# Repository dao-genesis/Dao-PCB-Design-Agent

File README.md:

# Dao-PCB-Design-Agent

> 让 Agent 像 Cursor 写代码一样进入 EDA 底层,代替人类全流程、全模块推进 PCB 设计。
> 道法自然 · 无为而无不为。

一个仓库,**两条并行且互不耦合的演化路线**(鸡犬相闻,老死不相往来):各自独立入口、
各自依赖、互不破坏,可单独演进,也可在数据层串联。

```
                         Dao-PCB-Design-Agent
                                  │
          ┌───────────────────────┴───────────────────────┐
          ▼                                                 ▼
  路线 A · 嘉立创EDA 直连                          路线 B · KiCad / 代码化
  (在线 Web 编辑器, CDP 直驱)                      (本地引擎, 代码生成 PCB)
          │                                                 │
   lceda_bridge/                                  pcb_brain/   (21 DNA 模板 → .kicad_pcb/Gerber/BOM)
     └ cdp_studio/  ← 冷启动底座                  schematic_dao/ (原理图道 → 四件套资料包)
       (CDP 直驱 _EXTAPI_ROOT_ + 登录态固化)       kicad_origin/  (KiCad 本源直连)
```

---

## 路线 A · 嘉立创EDA 直连(在线 Web · CDP)

经 Chrome 远程调试(CDP)在 `pro.lceda.cn/editor` 主页面上下文直接调用官方扩展 API
(挂在 `window._EXTAPI_ROOT_`,91 个命名空间),无需安装扩展/沙箱,执行→反馈→呈现三面归一。

- **冷启动底座**:[`lceda_bridge/cdp_studio/`](./lceda_bridge/cdp_studio/README.md) ——
  全新 VM 一条命令落到"已登录、可直驱"状态:
  ```bash
  python lceda_bridge/cdp_studio/cold_start.py
  ```
  登录态/凭据走加密 secret(`JLC_PHONE` / `JLC_PASSWORD` / `JLC_SESSION_B64`)注入,
  仓库内不存任何明文。后续会话只需手机号+密码即可承接。
- **桥接全景**:[`lceda_bridge/README.md`](./lceda_bridge/README.md)(五层穿透)。

## 路线 B · KiCad / 代码化(本地引擎)

代码即电路:从 DNA 模板/原理图工程一键生成可打样的 PCB 与全套制造资料。

- **PCBBrain**:[`pcb_brain/`](./pcb_brain/) —— 21 个 DNA 模板 → `.kicad_pcb`/Gerber/BOM/iBoM。
  ```python
  from pcb_core import PCB        # 统一门面
  ```
- **原理图道**:[`schematic_dao/`](./schematic_dao/) —— `SchematicProject` → 论文级四件套。
  ```bash
  python -m schematic_dao build <project>
  ```
- **KiCad 本源**:[`kicad_origin/`](./kicad_origin/)。

> 两线可在数据层串联:SchematicProject(论文级)→ DNA(布局级)→ PCB 打样下单。

---

## 仓库导航

| 目录 | 路线 | 说明 |
|---|---|---|
| `lceda_bridge/` | A | 嘉立创EDA 直连 + 冷启动底座(`cdp_studio/`) |
| `pcb_brain/` | B | DNA 模板 + 全闭环流水线(PCB) |
| `schematic_dao/` | B | 原理图道(四件套资料包) |
| `kicad_origin/` | B | KiCad 本源直连 |
| `_JLC_READY/` | 共用 | 23 个成品板模板(嘉立创打样就绪) |
| `实战/` | 共用 | 实战项目(1500W PFC、物流车控制系统等) |
| `docs/` | — | 总体方案与调研(全链路实现方案、线上资源参考) |
| `_local_launchers/` | — | 用户本机桌面启动器(指向本地 `D:\`/`Z:\` 路径,仅本机可用) |

- 架构与资源总览:[`_INDEX.md`](./_INDEX.md)
- Agent 操作手册:[`_AGENT_GUIDE.md`](./_AGENT_GUIDE.md)
- 交接说明:[`HANDOFF.md`](./HANDOFF.md)

## 仓库内入口脚本

- `lceda.cmd` / `lceda.ps1` —— LCEDA Bridge CLI(`lceda <subcmd>`,任意目录可用)。

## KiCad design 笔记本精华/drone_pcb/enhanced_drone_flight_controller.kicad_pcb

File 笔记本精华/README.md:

# 📁 项目模板说明

这个目录包含了各种SKiDL项目模板，帮助您快速开始新的PCB设计项目。

## 🎯 可用模板

### 1. **新项目模板.py** ⭐
- **用途**: 通用项目起始模板
- **包含**: 基础电路结构、LED控制、电源管理
- **特点**: 完整的注释、错误处理、自动化输出

### 2. **即将添加的模板**:
- `微控制器项目模板.py` - MCU核心电路
- `电源管理模板.py` - 电源转换电路  
- `传感器接口模板.py` - 传感器连接电路
- `通信接口模板.py` - UART/SPI/I2C接口

## 🚀 使用方法

### 快速开始
```bash
# 1. 复制模板到项目目录
cp templates/新项目模板.py projects/我的新项目.py

# 2. 编辑项目信息
# 修改文件中的PROJECT_NAME、AUTHOR等变量

# 3. 运行项目
cd projects
python 我的新项目.py
```

### 自定义步骤
1. **修改项目信息**:
   ```python
   PROJECT_NAME = "我的LED控制器"
   PROJECT_VERSION = "1.0.0" 
   AUTHOR = "张三"
   DESCRIPTION = "基于Arduino的LED控制电路"
   ```

2. **调整电路参数**:
   ```python
   VCC_VOLTAGE = 12.0  # 改为12V电源
   LED_CURRENT = 30e-3  # 改为30mA LED
   ```

3. **添加元件**:
   ```python
   # 在define_components()函数中添加
   components['switch'] = Part('Switch', 'SW_Push',
                               ref='SW1',
                               footprint='Button_Switch_THT:SW_PUSH_6mm')
   ```

4. **修改连接**:
   ```python
   # 在connect_circuit()函数中添加连接
   switch[1] += mcu['D2']  # 按钮连接到D2引脚
   switch[2] += gnd       # 另一端接地
   ```

## 📋 模板功能特性

### ✅ 包含的功能
- **自动计算**: LED限流电阻自动计算
- **错误处理**: 完善的异常处理机制
- **设计检查**: 自动DRC检查
- **多种输出**: 网表、ERC报告、BOM清单
- **中文注释**: 详细的中文说明

### 🎨 文件输出
```
output/
└── 项目名/
    ├── 项目名.net      # KiCad网表文件
    ├── 项目名.erc      # 电气规则检查报告
    └── 项目名_bom.txt  # 物料清单
```

## 🔧 配置说明

### KiCad库路径
确保在根目录的`config.py`中配置了正确的KiCad路径:
```python
KICAD_PATHS = [
    "C:/Program Files/KiCad/8.0/share/kicad/symbols",
    "C:/Program Files/KiCad/8.0/share/kicad/footprints",
]
```

### 元件库选择
模板使用标准的KiCad库:
- `Device` - 基础元件 (R, C, L, LED等)
- `MCU_Module` - 微控制器模块
- `Connector` - 连接器
- `Switch` - 开关按钮

## 🎓 学习建议

### 新手建议
1. 从`新项目模板.py`开始
2. 逐步修改参数，观察变化
3. 理解每个函数的作用
4. 学会查看ERC报告

### 进阶技巧
1. 创建自定义组件函数
2. 使用Python循环生成重复电路
3. 实现参数化设计
4. 添加仿真支持

## 🔍 故障排除

### 常见问题
1. **符号库找不到**: 检查config.py配置
2. **网表生成失败**: 检查元件连接是否正确
3. **ERC错误**: 查看未连接的引脚

### 调试技巧
```python
# 添加调试信息
print(f"元件 {part.ref}: {len(part.pins)} 个引脚")
print(f"网络 {net.name}: {len(net.pins)} 个连接")
```

## 📚 参考资源

- [SKiDL官方文档](https://devbisme.github.io/skidl/)
- [KiCad符号库](https://kicad.github.io/symbols/)
- [项目主README](../README.md)

---

**💡 提示**: 每次创建新项目时，建议复制模板并重命名，而不是直接修改模板文件。

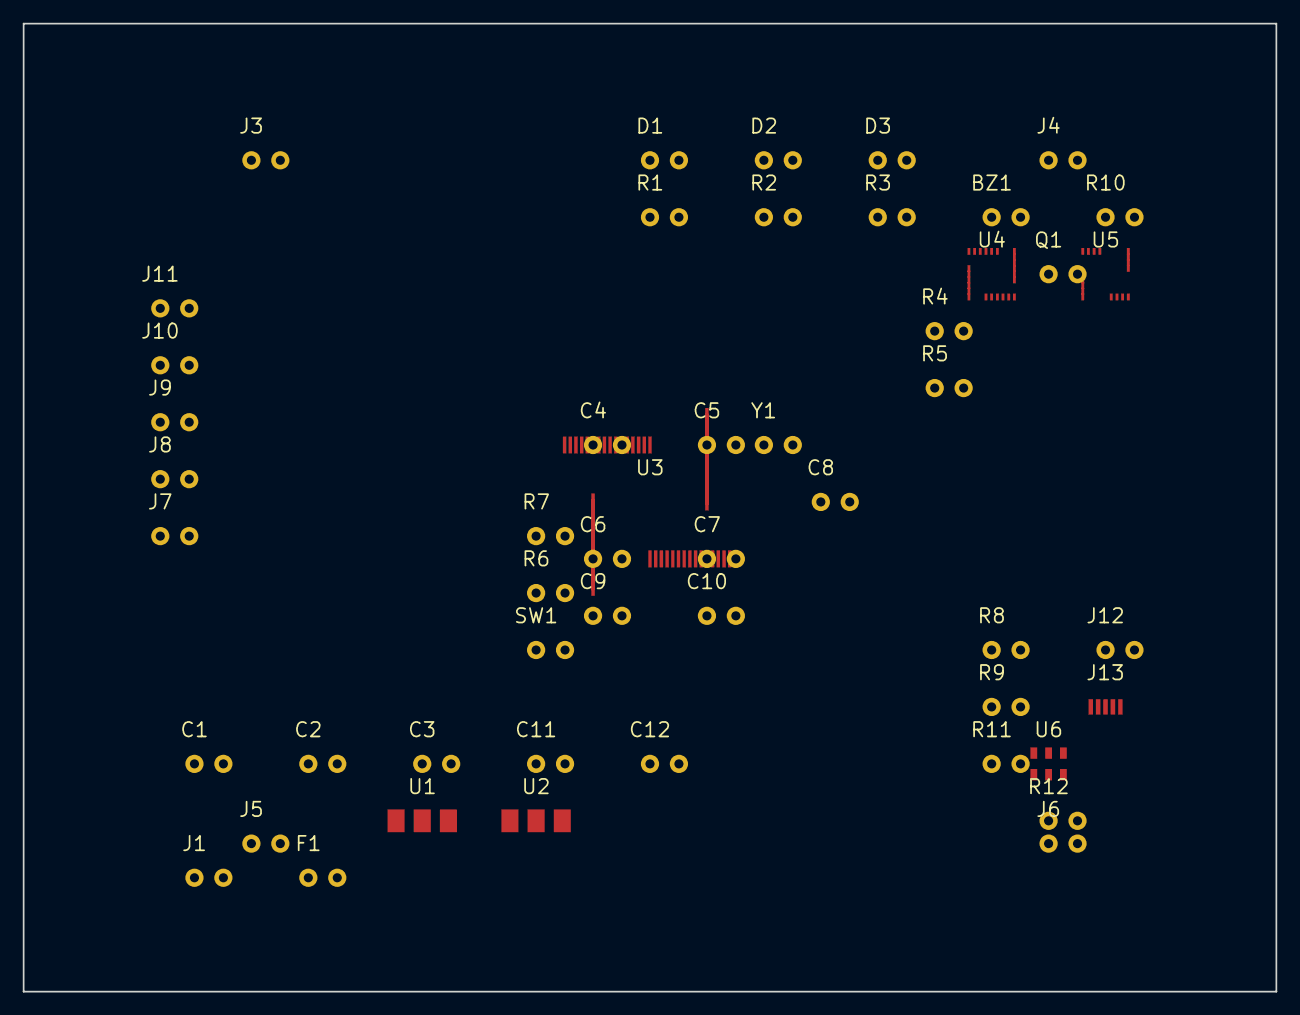
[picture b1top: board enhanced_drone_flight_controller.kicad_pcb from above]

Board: 2 copper layers, 110.0 x 85.0 mm, 50 parts (0 on the bottom side), 25 nets, no tracks yet.

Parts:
BZ1: Buzzer; Buzzer_12x9.5RM7.6
C1: 1000uF; CP_Radial_D8.0mm_P3.50mm
C2, C3: 100uF; C_1206_3216Metric
C4, C5, C6, C7, C8: 100nF; C_0603_1608Metric
C9, C10: 22pF; C_0603_1608Metric
C11: 10uF; C_0603_1608Metric
C12: 1uF; C_0603_1608Metric
D1: Power; LED_0603_1608Metric
D2: Status; LED_0603_1608Metric
D3: GPS_Lock; LED_0603_1608Metric
F1: 5A; Fuse_1206_3216Metric
J1: Battery; JST_XH_B2B-XH-A_1x02_P2.50mm_Vertical
J3: ESC1; PinHeader_1x03_P2.54mm_Vertical
J4: ESC2; PinHeader_1x03_P2.54mm_Vertical
J5: ESC3; PinHeader_1x03_P2.54mm_Vertical
J6: ESC4; PinHeader_1x03_P2.54mm_Vertical
J7: GPS; PinHeader_1x04_P2.54mm_Vertical
J8: Telemetry; PinHeader_1x04_P2.54mm_Vertical
J9: RC_RX; PinHeader_1x08_P2.54mm_Vertical
J10: I2C_EXP; PinHeader_1x04_P2.54mm_Vertical
J11: SPI_EXP; PinHeader_1x06_P2.54mm_Vertical
J12: SWD; PinHeader_1x04_P2.54mm_Vertical
J13: USB_Config; USB_Micro-B_Molex_47346-0001
Q1: NPN; TO-92_Inline
R1, R2, R3: 330; R_0603_1608Metric
R4, R5: 4.7k; R_0603_1608Metric
R6, R7, R8: 10k; R_0603_1608Metric
R9: 3.3k; R_0603_1608Metric
R10: 1k; R_0603_1608Metric
R11: 100; R_0603_1608Metric
R12: 2.2k; R_0603_1608Metric
SW1: Reset; SW_PUSH_6mm
U1: 5V_Reg; SOT-223-3_TabPin2
U2: 3V3_Reg; SOT-223-3_TabPin2
U3: Flight_Controller; LQFP-64_10x10mm_P0.5mm
U4: IMU; InvenSense_QFN-24_4x4mm_P0.5mm
U5: Magnetometer; LGA-16_3x3mm_P0.5mm
U6: USBLC6-2SC6; SOT-23-6
Y1: 8MHz; Crystal_HC49-4H_Vertical

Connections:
0: U3.1, U3.2, U3.3, U3.4, U3.8, U3.9, U3.10, U3.20, U3.21, U3.22, U3.38, U3.40, U3.47, U3.48, U3.51, U3.52, U3.53, U3.54, U3.55, U3.56, U3.57, U3.61, U3.62, U3.63, U4.1, U4.2, U4.3, U4.4, U4.5, U4.6, U4.7, U4.10, U4.14, U4.15, U4.16, U4.17, U4.19, U4.20, U4.21, U4.22, U5.1, U5.2, U5.3, U5.4, U5.5, U5.6, U5.7, U5.8, U5.9, U5.10, U5.11
1: C1.1, F1.1, J1.1, R8.1
2: C1.2, C2.2, C3.2, C4.2, C5.2, C6.2, C7.2, C8.2, C9.2, C10.2, C11.2, C12.2, D1.2, D2.2, D3.2, J1.2, J3.2, J4.2, J5.2, J6.2, J7.2, J8.2, J9.2, J10.2, J11.2, J12.2, J13.4, J13.5, Q1.2, R7.2, R9.2, R12.2, SW1.2, U1.2, U2.2, U3.12, U3.14, U3.27, U4.8, U4.11, U4.18, U5.16, U6.1, U6.6
3: F1.2, U1.1
4: BZ1.2, C2.1, C11.1, J3.1, J4.1, J5.1, J6.1, J9.1, J13.1, U1.3, U2.1
5: C3.1, C4.1, C5.1, C6.1, C7.1, C8.1, C12.1, J7.1, J8.1, J10.1, J11.1, J12.1, R1.1, R4.1, R5.1, R6.1, R11.1, U2.3, U3.11, U3.13, U3.19, U3.28, U3.50, U3.64, U4.9, U4.13, U5.13, U6.3, U6.4
6: C9.1, U3.5, Y1.1
7: C10.1, U3.6, Y1.2
8: R6.2, SW1.1, U3.7
9: R7.1, U3.60
10: R4.2, U3.59, U4.23, U5.14
11: R5.2, U3.58, U4.24, U5.15
12: U3.23, U4.12
13: U3.24, U5.12
31: R11.2, U3.29
34: D1.1, R1.2
35: R2.1, U3.15
36: D2.1, R2.2
37: R3.1, U3.16
38: D3.1, R3.2
39: R8.2, R9.1, U3.17
40: R10.1, U3.18
41: Q1.1, R10.2
43: J13.2, U3.44, U6.2
44: J13.3, U3.45, U6.5

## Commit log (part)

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2026-06-24 Dao PCB Design Agent - PCBBrain + SchematicDao + KiCad Origin + LCEDA Bridge - 21 DNA templates - 16 MCP tools - 23/23 verify PASS
2026-06-25 PCB末公里: 精确via-in-pad桥避让他网过孔+真实线段相交净空, 无网焊盘障碍; 19/21 unconn=0 (drc=0)
2026-06-25 fix(layout): auto_layout 改用外接框(courtyard)避让 → 真实DRC违规清零
    旧 auto_layout 只看元件中心点距(math.hypot<MIN_SPACING), 忽略封装外形, 致大封装
    (2x08排针/QFP等)与邻居焊盘物理重叠, 接入真实DRC后暴露 R001 焊盘重叠 21~26处/板。
    - footprint_pads: 新增 footprint_extent() 由焊盘外接框推元件半宽/半高
    - circuit_dna.auto_layout: 中心点距判据 → 外接框不重叠判据, 按真实外形步进
    - 真实DRC复测: gd32f103 21→0, stm32f103 21→0(自由能69→6), drone_flight 26→5;
    全量21模板DRC违规全部清零, 剩余误差清一色为异形封装pad缺口或D类坏数据
2026-06-25 fix(dna): 修复 D 类数据损坏 — 旧式4参Comp约定的封装缺失
    根因: 5个模板(esp32s3_rs485_can/stm32h743_core/industrial_power/lcd_tft_43/
    safety_protection)以旧式 Comp(ref,value,group,pos) 4参约定写就, 漏写 fp_lib/fp_name,
    致 group 落入 fp_lib 槽、pos 落入 fp_name 槽, 全部元件无封装、位置重叠于一点。
    - 新增 recover_legacy_comps(): 把 group/pos 归位(本就在数据里,只是放错槽),
    由 value/网表反推缺失封装; auto_layout 开头调用
    - 新增 infer_footprint(): 高置信器件型号映射(SOIC/SOT/QFP/二极管/熔丝/晶振) +
2026-06-25 feat(footprint): 模组值=官方封装名时取官方库真实封装 (esp32s3 62→32, 总 507→477)
    infer_footprint 末环honest兜底: 若器件值恰是官方库某封装精确名(如 ESP32-S3-WROOM-1),
    取该真实封装 (footprint_pads.official_fp), 配合符号库 pin-name 解析 → 模组整片接网。
    仍找不到的模组/异形件(Ebyte E73/Ai-Thinker Ra-02/FPC/GT911)按诚实留白, 不臆造。
2026-06-25 feat(symbol): 符号自带权威封装修复错配 + SPI-flash Dn↔IOn (432)
    - footprint_of(): 取 KiCad 符号标注的规范器件-封装配对 (权威源)
    - repair_footprints(): 仅当当前封装覆盖不了网表所需脚、且符号封装能覆盖时替换
    · CH224K SOP-8→SSOP-10-1EP · MAX30102 →OLGA-14 · 等
    - _canon: SPI NOR flash 数据线 Dn↔IOn (JEDEC 通用; 歧义剔除+精确优先保安全)
    效果: 总自由能 451→432; rp2040 24→16 · usb_c 12→6 · drone_aerial 46→36;
    连通性全面改善零回退; smartwatch +5 纯为更大真实封装引入的 DRC(下一轮布局消除)
2026-06-25 feat(symbol): 记法等价3连+权威兄弟件别名 (344→320)
    - VIN↔VI / VOUT↔VO 稳压器输入输出等价 (industrial_power 18→14)
    - RST↔RESET 复位脚核等价
    - 有源低脚登记裸核别名 (NSS↔~{NSS}, RESET↔~{RESET}); 仅无冲突时, +/-差分不并
    - _VALUE_ALIAS: Ra-02 借 pin-compatible 兄弟件 Ai-Thinker-Ra-01 符号/封装
    (官方文档明示二者引脚兼容, 仅天线不同) → lora_sx1276_gateway 22→2
    均为记法/兼容性桥接, 歧义即留白, 非臆造。零回退 (交付仍7/21)。
2026-06-25 feat: ESP32-S3 GPIO19/20↔USB D-/D+ 芯片专属脚别名 + USB-C检测放宽 (296→286)
    - _PIN_ALIAS: ESP32-S3 GPIO19/GPIO20 即原生 USB D-/D+ (同一焊盘, Espressif datasheet)
    - resolve_usb_c: 检测放宽到 'USB_C' 子串 (捕获 USB_C_CONN)
    效果: esp32s3_rs485_can 16→6 (余 TJA1050 无KiCad符号)。
2026-06-26 fix(drone_aerial_h743): resolve sensor pinouts + eliminate pad shorts
    predictive-coding loop drives free_energy down to 178; 18/21 delivered.
    - symbol_lib: add ICM-42688-P datasheet pinmap (TDK DS-000347 section 4.1)
    - circuit_dna: INA226 footprint MSOP-8 -> TSSOP-10 (matches KiCad symbol)
    - circuit_dna: split VBAT/VBAT_FUSED/VBUS_SENSE nets (remove R1/U3 shorts)
    - circuit_dna: sensor nets now use functional pin names (AP_SCLK, SDA...)
    resolved via KiCad symbols + datasheet fallback, not raw pad numbers
2026-06-26 feat(web): 全板视觉审视静态站 (SVG渲染+诚实DRC+参数) → docs/ 可GitHub Pages公网托管
2026-06-26 fix(router): 平面铺铜异网孔体keepout优先于本网焊盘力保 → 物理短路清零
    pour_plane 中'本网焊盘恒可达'(blocked -= own_pad_cells)优先级压过异网通孔 keepout,
    当 GND 焊盘紧邻异网缝合过孔时, GND 铜格被强制保留 + 半格栅格外扩(±0.05mm),
    铜箔溢出焊盘边缘压住孔体 → 0.02mm 物理短路(DRC R007 几何盲区查不到)。
    修复(因而制之·物刑器成): 异网通孔(贯穿全层)的 keepout 优先级提到本网焊盘之上,
    孔体周围必抠空; 本网焊盘仍经其自身缝合过孔(孔心入种子)连通平面, 故不引入开路。
    新增 _audit.py: 全方位物理短路审计(4类: 孔-线/孔-孔/铜区-孔/铜
2026-06-26 feat(mcp): 暴露通用 design_spec/pipeline_spec 为一等 MCP 工具
    把已实现的'任意 spec/网表→0→1全闭环+预测编码裁决'能力接入 MCP 工具层,
    让任意 AI 客户端(Devin / VSCode·KiCad 内的 DAO Bridge)都能驱动从没见过的
    设计走完整链路, 而非被21模板注册表绑死。反者道之动: 基础设施通用化。
    - design_spec: dict/.json/.yaml/.net → DNA → 布局布线 → .kicad_pcb
    - pipeline_spec: 任意 spec → 真实DRC/Gerber/BOM/CPL/iBoM → reconcile 交付裁决
    返回 delivered(自由能=0才True)/free_energy/next_action
2026-06-26 kicad_origin: re-export full 5-layer + dao API at top level; add Cursor-for-PCB MVP architecture doc
    - Top-level __init__.py previously exported only Layer 0; canonical imports
    (Board, run_drc, Dao, LiveKiCad deps) were broken and self-test could not run.
    Re-export lib/pcb/engine/app + dao (83 symbols) and fix \K SyntaxWarning (raw docstring).
    - Add _CURSOR_FOR_PCB.md: MVP agent-loop architecture (perceive/plan/act/verify/reflect)
    mapping VS Code->Cursor onto KiCad->Dao-PCB, grounded in real LiveKiCad/run_drc/Feedback APIs.
2026-06-26 feat(copilot): 对话框升为可独立托管的主面 + URL 参数驱动多轮
    - 桥服务器新增 /ui /dialog 路由直托 iframe 对话框(对用户只增加一个对话框)
    - iframe 同源优先解析桥地址, 支持 ?q= 一键自动发送 / ?s= 固定会话 / ?dir= 续接产物目录
    - 据此在嘉立创EDA Pro 母体上真机跑通: 一句话→全链路→自由能32→0→已交付, 多轮核验 fe=0 保持
2026-06-27 fix(engine): 实践难板暴露并修复两处真实缺陷 — 网表ERC(焊盘多网冲突) + 过孔守工艺下限
    我即PCB Agent, 拿自己的引擎设计STM32F103+USB+晶振+LDO难板(非模板)实践, 暴露:
    1) 同一焊盘被分到两网(物理短路)被静默吞掉 → pipeline_converge 追结构不可达目标,
    自由能永不归零。pcb_spec.validate_nets 升为一等ERC, 解析期当场指明冲突焊盘+冲突网,
    spec/json/yaml/.net 四条摄入通路全覆盖。
    2) 细间距缝合过孔被收窄到 0.30/0.15 (孔径<0.20 环宽<0.10), 跌破 JLCPCB 工艺下限。
    抬到 0.40/0.20 (孔0.20+双边环0.10), 与异网间距仍由 clearance 搜索+safe+重布兜底。
2026-06-27 pinmap: 命名引脚→脚号 (从 KiCad 符号库取真理, 保守对齐) — 解 GAP1 头号瓶颈
    - 新工具 kicad_origin/pcb/pinmap.py: resolve_named_pins(nets, components).
    据元件 value 经 SymbolIndex 认出 KiCad 符号, list_pins 取 name↔number,
    把 DNA 网表里 IC 的命名引脚 (SCLK/SCSn/...) 翻成封装脚号.
    - 保守对齐: 精确+归一化匹配 (剥 ~{} 低有效/分隔符/大小写; SCSn↔~{SCS}),
    电源/地逻辑网扇出到同名多脚; 对不准的 (VCC↔VDD/AVDD/差分) 不猜, 留空并报候选.
    - design_loop 加 --pinmap; 实测 w5500 真 DRC: 绑定 28→43 (+15脚), 真飞线 15→30,
2026-06-27 fix(lceda_bridge): CdpTransport.connect accepts browser_ws_url (ws-only target discovery)
    dao_connector.connect() passes browser_ws_url= into CdpTransport.connect for the
    lceda-pro 'HTTP /json blocked' path, but the classmethod didn't accept it ->
    TypeError on every bus/cdp connect against a live EDA. Add the param; when HTTP
    /json/list is empty and a browser ws is known, enumerate page targets via
    Target.getTargets and connect to the page ws directly.
2026-06-27 feat: KiCad 9 native integration via pcbnew SWIG bridge
    - Board.empty() updated to KiCad 9 format (version 20241229, correct layer IDs)
    - New swig_bridge.py: DNA → pcbnew SWIG → native .kicad_pcb generation
    - Uses real KiCad library footprints (SOT-223, 0805, QFP-64, etc.)
    - kicad-cli DRC/SVG/Gerber/3D export wrappers
    - full_native_pipeline(): DNA → native board → DRC → SVG in one call
    - All 21 DNA templates: 0 DRC violations via kicad-cli (native KiCad 9 DRC)
2026-06-27 feat(eda_flow): 全流程编排打通(建工程→放件→原理图转PCB→DRC→Gerber/BOM/贴片坐标)
    - eda_flow.Flow: 账号层(REST)+编辑器层(extapi)+GUI兜底(CDP) 归一流水线
    - 实战发现并处理:importChanges 需点 Apply Changes(ui_click_text 自动确认);
    导出返回 Blob/File(页内读 base64 落盘);placeComponentWithMouse 需画布落子+Esc
    - 实测从零建工程→放 R/C/LED→同步 PCB→DRC通过→导出有效 Gerber(全层)+BOM.xlsx+贴片坐标
    - PHASE4_FINDINGS/README 更新;.gitignore 忽略生成产物
2026-06-27 docs(findings): 更正连通判断 — 两网均正确传播,N_CL desync 系手工改动所致
    - 更正:connect_pins 后首次 importChanges 即把 N_RC/N_CL 都同步进 PCB
    - 正确姿势:手工改动后重新 update_pcb_from_schematic + prepare_pcb_nets 得一致网络态
    - 核对连通优先看 pcb_Net(getNetlist 偶发 NO_RESULT)
    - 逐网自动布线拦路:未布网络的焊盘/飞线成员查询尚不稳定
2026-06-27 feat(ne555): 复杂工程端到端实践 — 无碰撞自动布线,6网正确传播PCB
    - build_ne555.py: 从0造NE555闪烁器(scaffold/place/wire/sync)
    - 攻克边界: 对角线导线被拒/端点落脚短路/排阻误选/放件ghost
    - 逃逸+横轨布线算法: 6网全部正确传播(pad计数与设计吻合)
    - findings 九章记录全部底层发现
2026-06-28 feat(build_mcu): 第四块板 ATmega328P最小系统——32脚TQFP最大压测
    - build_mcu.py: ATMEGA328P-AU(TQFP-32 0.8mm)+16MHz晶振+2x22pF+ICSP 2x3排座+复位上拉+LED
    - 10器件/9网(GND 11成员/VCC 7成员大扇出), 一键build跑通:
    放件10/10→wire81→sync 9网missing[]→程序化板框→autoroute 129铜线+11过孔→DRC通过→全导出
    - 证明引擎在高脚数细间距IC上稳; PHASE4_FINDINGS 第十四章
2026-06-28 merge dao-kicad live real-KiCad engine into the source repo
    Consolidate the previously-separate dao-kicad repo into Dao-PCB-Design-Agent as
    dao_kicad/: the live engine that drives a real KiCad install (pcbnew SWIG board
    build + headless freerouting DSN/SES autoroute + official IPC live board + an
    in-pcbnew chat panel), complementing kicad_origin/ (pure-Python reverse).
    Cold-start full chain validated on KiCad 10.0.4 + Temurin JDK 25 + freerouting
    2.2.4: verify_all.py 49/49 checks, 14/14 boards DRC-clean; pytest 68 passed.
2026-06-28 findings(ch.22.6/22.7): root cause of dense-board connection errors = Freerouting-SES layer-change via not recognized by JLC connectivity (DSIG_N=2 single-layer islands bridged by a 0.00mil-coinciden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
2026-06-28 feat(fabricate): wire KiBot backend end-to-end (board -> gerber/drill/pos)
    fabricate now has a second, CI-grade backend behind the same interface:
    _kibot_fab() drives 'python -m kibot' on a board-only default config (no
    schematic required) and reports the gerbers produced. Builtin kicad-fab stays
    the default (priority 55 > 50); KiBot is selected via prefer='kibot'.
    Proven on the SKiDL divider board -> 24 gerbers + drill + placement CSVs.
    Fixes the kibot/kibot-bom probes (importable module, not a PATH exe) and the
2026-06-28 setNetlist round-trip: write path confirmed callable (returns True); document nested-encoding schema precision as next step
2026-06-28 Exhaust programmatic import: rpc family (importProjectByProjectFile/createFolder) no-ops in headless CDP (File serialization / user-gesture boundary). Reliable path = UI Import wizard + CDP file-choo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
2026-06-28 registry: wire netlist + drc builtin stages as runnable backends
    netlist and drc were declared live but lacked invokes, so the brain
    could not call them through registry.run. Add _netlist_export (kicad-cli
    sch->netlist) and _drc_run (LiveKiCad.drc, clean=0err+0unconn), wire both.
    8 capability domains now runnable via the uniform contract. +2 mocked
    tests (13 registry, verified live on complex_hierarchy).
2026-06-28 feat(reverse): deconstruct real boards + fix DRC false-positives
    REVERSE track on KiCad demo kit-dev-coldfire-xilinx_5213 (160 fp / 278
    nets / 2935 tracks / 253 vias):
    - examples/reverse_analysis.py: extract (pcbnew) -> roundtrip fidelity
    -> our pure-py kernel -> gold kicad-cli DRC, all quantified.
    roundtrip is connectivity_identical (209 net groups preserved).
    - Exposed defect: our DRCEngine reported 79 geometry errors on a board
2026-06-29 ci: add Python syntax gate (whole-repo py_compile + documented quarantine)
    - New GitHub Actions CI gates every tracked .py via py_compile on push/PR,
    so new syntax errors can't merge — establishes the repo's auto-PR line.
    - Fix lceda_bridge/demos/ui_demo.py: make module docstring raw (Windows paths
    in usage examples were parsed as invalid \u escapes -> SyntaxError).
    - Quarantine 2 files truncated-at-first-commit with unrecoverable bodies
    (pcb_brain/pcb_intent.py, pcb_self_loop.py) via .github/ci-syntax-ignore.txt;
2026-06-29 feat(eda_flow): programmatic net-level copper router (fusion 融合, full-chain)
    Reverse-eng: on the PCB, net binding lives on COMPONENT PINS
    (pcb_PrimitiveComponent.getAllPinsByPrimitiveId -> each pin carries net/x/y);
    pcb_PrimitivePad.getAll returns only free pads, not component pins, so it reads
    empty for synced nets.
    New (no GUI, no board-outline requirement — unlike autoroute_gui):
    - pcb_pins_by_net(net=None): gather {net: [(x,y)...]} from all component pins.
2026-06-29 feat(eda_flow): GND copper pour works on real placed boards -> DRC clean
    auto_ground_pour computed its bbox from free pads (pcb_PrimitivePad.getAll), which
    is empty on a real placed board (pads are bound to component pins, not free). Added
    a fallback that derives the bbox from component pins (getAllPinsByPrimitiveId) so it
    works on actual boards.
    Live proof build_pour_det.py (RESULT PASS): 3 resistors, NET_1 signal routed top
    (escape), GND left for a copper plane. Before pour DRC = 3 Connection Errors (GND
